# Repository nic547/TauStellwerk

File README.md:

# TauStellwerk

TauStellwerk is a open-source software project for controlling model railways.
It is intended to provide a intuitive user interface for easy and quick edits and control of a model railway.
It is not intended to be a competitor to more complex software like JMRI, TrainController or similar, but rather
an alternative to manufacturer-provided applications.

If you have any questions, feedback or any other comments, feel free to open a issue or pm me(nic547) on discord.

## Overview

The software is still in an experimental state. There might be some fundamental changes that break existing databases or installations.
Currently there are no prebuilt binaries available.

Currently supported Command Stations:

- ESU Command Station (ECoS)
- DCC++ EX (via USB)

## Requirements
TauStellwerk requires the ASP.NET Core Runtime 8.0 to be installed.
See the [Microsoft .NET Download page](https://dotnet.microsoft.com/en-us/download/dotnet/8.0) for downloads and installation instructions.

### MacOS/iOS

Using the cross-platform .NET software framework does mean that the TauStellwerk-Software should run on MacOS/iOS. Unfortunately I do not have access to either OS, so I cannot test on either OS.

### Webserver

Core of the TauStellwerk software is the TauStellwerk.Server component. It handles communication between the CommandStation and the clients. Can, for example, be run on a Raspberry Pi.

For the sake of simplicity, there are no "accounts". Any user can choose whatever username he desires. Access control has be done by restricting access to the server.

### Webapp

The Webapp is based on Blazor WebAssembly and should run on any recent version of the commonly used Browsers. Generally the application is tested with current versions of Chrome, Firefox and Edge. It's expected that the webapp will not necessarily have feature-parity with the dedicated applications and be more of a "lite" version.

### Desktop Application

Uses .NET and AvaloniaUI. Connects to the TauStellwerk.Server. Tested on Linux and Windows.

### Mobile App

Planned but not started. Initially MAUI was intended to be used, currently waiting to see how MAUI vs UNO vs AvaloniaUI for mobile apps pans out.

## Licences

Unless noted otherwise, this project is licensed under the GNU GPLv3, see [here](/LICENSE) for more details.

## Contributing

All contributions are welcome. As I'm currently the sole user and developer, documentation isn't a huge focus for me, so feel free approach me with any potential questions.

## Acknowledgements

JetBrains has been kind enough to provide me with a free open-source license for their products as part of their [open source support program](https://jb.gg/OpenSourceSupport). I'm using Rider for development and can only recommend it.

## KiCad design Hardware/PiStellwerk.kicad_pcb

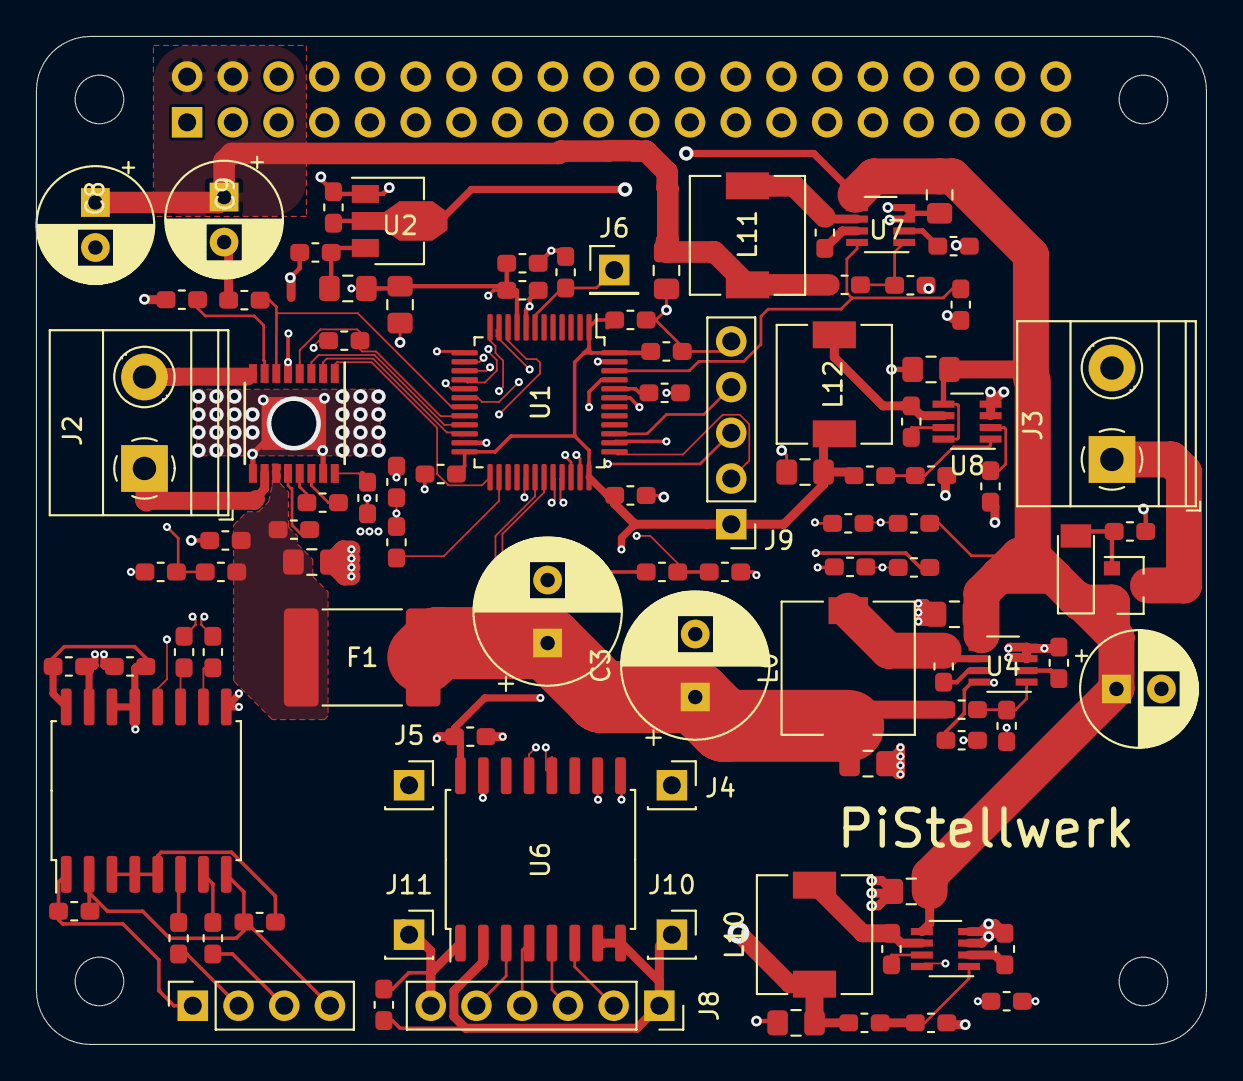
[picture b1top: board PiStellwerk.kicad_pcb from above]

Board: 4 copper layers, 65.0 x 56.0 mm, 104 parts (1 on the bottom side), 78 nets.

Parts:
C1, C4, C5, C6, C18, C19, C20, C27, C28, C29, C30, C31, C32, C33, C35: 35V/100nF; C_0603_1608Metric_Pad1.05x0.95mm_HandSolder
C2, C10, C12, C13, C14, C24: 35V/10uF; C_0805_2012Metric_Pad1.15x1.40mm_HandSolder
C3, C36: 35V/220uF; CP_Radial_D8.0mm_P3.50mm
C7, C17, C21, C26: 6.3V/47uF; C_0805_2012Metric_Pad1.15x1.40mm_HandSolder
C8, C9: 6.3V/470uF; CP_Radial_D6.3mm_P2.50mm
C11, C15, C16, C25, C34: 35V/10nF; C_0603_1608Metric_Pad1.05x0.95mm_HandSolder
C22, C23: C; C_0603_1608Metric_Pad1.05x0.95mm_HandSolder
C41: 35V/100uF; CP_Radial_D6.3mm_P2.50mm
D1: 12V; D_MiniMELF
F1: 24V/3A; Fuse_2920_7451Metric
FB1: Ferrite_Bead; L_0805_2012Metric_Pad1.15x1.40mm_HandSolder
H1, H2, H3, H4: MountingHole; MountingHole_2.7mm_M2.5
J1: Conn_02x20_Odd_Even; PinSocket_2x20_P2.54mm_Vertical
J2, J3: Screw_Terminal_01x02; TerminalBlock_Phoenix_MKDS-1,5-2-5.08_1x02_P5.08mm_Horizont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
J4, J5, J10, J11: Conn_01x01; PinSocket_1x01_P2.54mm_Vertical
J6: Conn_01x01; PinHeader_1x01_P2.54mm_Vertical
J7: Conn_01x04; PinSocket_1x04_P2.54mm_Vertical
J8: Conn_01x06; PinSocket_1x06_P2.54mm_Vertical
J9: Conn_01x05; PinHeader_1x05_P2.54mm_Vertical
L0: 10uH; L_7.3x7.3_H4.5
L10, L11, L12: 3.3uH; L_6.3x6.3_H3
Q1: Q_PMOS_GDS; SOT-23
R1: 2K42; R_0603_1608Metric_Pad1.05x0.95mm_HandSolder
R2, R3, R10, R12, R13, R18, R20, R21, R22, R25, R26: R; R_0603_1608Metric_Pad1.05x0.95mm_HandSolder
R4: 100kOhm; R_0603_1608Metric_Pad1.05x0.95mm_HandSolder
R5, R6, R7, R11: 10K; R_0603_1608Metric_Pad1.05x0.95mm_HandSolder
R8, R14, R16, R19: 100K; R_0603_1608Metric_Pad1.05x0.95mm_HandSolder
R9: 3.4K; R_0603_1608Metric_Pad1.05x0.95mm_HandSolder
R15, R17: 13.7K; R_0603_1608Metric_Pad1.05x0.95mm_HandSolder
R30: 22.1K; R_0603_1608Metric_Pad1.05x0.95mm_HandSolder
R40, R41, R42, R43: 24R; R_0603_1608Metric_Pad1.05x0.95mm_HandSolder
R50, R51, R52, R53: 40K; R_0603_1608Metric_Pad1.05x0.95mm_HandSolder
TH1, TH2: Thermistor_NTC; R_0603_1608Metric_Pad1.05x0.95mm_HandSolder
U1: STM32F103C8Tx; LQFP-48_7x7mm_P0.5mm
U2: HT7533; SOT-89-3
U3: DRV8876; TSSOP-16-1EP_4.4x5mm_P0.65mm
U4, U7, U8, U9: SY8303; TSOT-23-8
U5: ADUM4160; SOIC-16W_7.5x10.3mm_P1.27mm
U6: ISO3088DW; SOIC-16W_7.5x10.3mm_P1.27mm

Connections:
3V3: C4.1, C26.1, C27.2, C28.2, C29.1, C31.1, C32.1, C33.1, J9.1, L12.1, R19.1, U1.1, U1.24, U1.36, U1.48, U5.13, U5.14, U5.16, U6.16
3VA3: C7.1, C34.2, C35.2, FB1.1, TH1.1, TH2.1, U1.9, U3.5
5V: C8.1, C9.1, C17.1, J1.2, J1.4, L11.1, R14.1
18V: C3.1, C13.1, C36.1, F1.1, L0.1, R8.1, R21.1
18V_FUSED: C1.1, C10.1, C22.2, F1.2, R18.1, U3.11
/3V3_UNFILTERED: C6.1, FB1.2, U2.3
/IMODE: R2.1, U3.7
/PMODE: R3.1, U3.16
/TRACK_A: J2.1, U3.10
/TRACK_B: J2.2, U3.8
/USB+: C18.1, J7.1, U5.1
/USB_GND: C18.2, C19.2, J7.4, U5.2, U5.8
/USB_VDD: C19.1, U5.3, U5.4, U5.5
ADC_IN1: R12.2, R13.1, U1.11
ADC_IN2: R21.2, R22.1, U1.12
ADC_IN3: R18.2, R20.1, U1.13
ENABLE_5V: R7.1, U1.46, U7.8
ENABLE_18V: R5.1, U1.38, U4.8
EN_SEC_5V: R11.1, U1.45, U9.8
GND: C1.2, C2.1, C3.2, C4.2, C5.2, C6.2, C7.2, C8.2, C9.2, C10.2, C12.1, C13.2, C14.1, C17.2, C21.2, C24.1, C26.2, C27.1, C28.1, C29.2, C30.2, C31.2, C32.2, C33.2, C34.1, C35.1, C36.2, C41.2, J1.6, J1.9, J1.14, J1.20, J1.25, J1.30, J1.34, J1.39, J3.2, J4.1, J9.5, R1.2, R2.2, R3.2, R4.2, R5.2, R6.2, R7.2, R9.2, R10.1, R11.2, R13.2, R15.2, R17.2, R20.2, R22.2, R30.2, R50.1, R51.1, R52.1, R53.1, U1.8, U1.23, U1.35, U1.47, U2.1, U3.9, U3.15, U3.17, U4.3, U4.4, U5.9, U5.15, U6.9, U6.10, U6.15, U7.3, U7.4, U8.3, U8.4, U9.3, U9.4
IN1: U1.25, U3.1
IN2: U1.22, U3.2
NTC1_ADC: R25.1, TH1.2, U1.10
NTC1_EN: R25.2, U1.26
NTC2_ADC: R26.1, TH2.2, U1.18
NTC2_EN: R26.2, U1.43
unnamed: C11.1, U4.7
unnamed: C11.2, L0.2, U4.6
unnamed: C15.1, U7.7
unnamed: C15.2, L11.2, U7.6
unnamed: C16.1, U9.7
unnamed: C16.2, L10.2, U9.6
unnamed: C20.1, J8.1, J10.1, U6.2, U6.7, U6.8
unnamed: C20.2, J8.6, J11.1, U6.1
unnamed: C21.1, J5.1, L10.1, R16.1
unnamed: C22.1, U3.12
unnamed: C23.1, U3.14
unnamed: C23.2, U3.13
unnamed: C25.1, U8.7
unnamed: C25.2, L12.2, U8.6
unnamed: C30.1, J6.1, U1.7
unnamed: D1.2, Q1.1, R4.1
unnamed: J3.1, Q1.3
unnamed: J7.2, R43.2
unnamed: J7.3, R42.1
unnamed: J8.2, U6.6
unnamed: J8.3, U6.5
unnamed: J8.4, U6.4
unnamed: J8.5, U6.3
unnamed: R6.1, U1.44
unnamed: R8.2, R9.1, U4.1
unnamed: R14.2, R15.1, U7.1
unnamed: R16.2, R17.1, U9.1
unnamed: R19.2, R30.1, U8.1
unnamed: R40.2, U5.11
unnamed: R41.1, U5.10
unnamed: R42.2, U5.7
unnamed: R43.1, U5.6
unnamed: R50.2, U7.2
unnamed: R51.2, U8.2
unnamed: R52.2, U9.2
unnamed: R53.2, U4.2
SPI_MISO: J1.21, U1.16
SPI_MOSI: J1.19, U1.17
SPI_SCLK: J1.23, U1.15
SPI_SS: J1.24, U1.14
SWCLK: J9.2, U1.37
SWDIO: J9.3, U1.34
TRACESWO: J9.4, U1.39
TRACK_CURRENT: R1.1, U1.19, U3.6
UART_RX: U1.31, U6.12
UART_TX: U1.30, U6.13
USB_D+: R41.2, U1.33
USB_D-: R40.1, U1.32
USB_PIN: U1.29, U5.12
VIN: C2.2, C5.1, C12.2, C14.2, C24.2, C41.1, D1.1, Q1.2, R12.1, U2.2, U4.5, U7.5, U8.5, U8.8, U9.5
nFault: R10.2, U1.20, U3.4
nSleep: U1.21, U3.3

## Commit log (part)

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2021-08-18 Bump Avalonia.Desktop from 0.10.6 to 0.10.7
    Bumps [Avalonia.Desktop](https://github.com/AvaloniaUI/Avalonia) from 0.10.6 to 0.10.7.
    - [Release notes](https://github.com/AvaloniaUI/Avalonia/releases)
    - [Commits](https://github.com/AvaloniaUI/Avalonia/compare/0.10.6...0.10.7)
    ---
    updated-dependencies:
    - dependency-name: Avalonia.Desktop
2021-08-20 Update build.sh, only use PublishSingeFile in Relase mode
    Also disable PublishSingleFile for CI
2021-08-24 Delete dependabot.yml
    Resolves #126
2021-08-24 Ensure correct command system status is loaded on startup
    The first StatusChanged event fired before the StatusService was subscribed.
    Instead the StatusSystem can now "ask" for the event.
    Resolves #119
2021-08-29 Replace "Random User $Number" with "Random $color $animal"
    IMHO the new random user names are much easier to remember then a long number. I'm not 100% happy with it, but failed to come up with something better.
    Resolve #132
2021-09-03 Add SonarScanner action .yml (#136)
    * Add SonarScanner action .yml
    * Update sonar.yml
    * Update sonar.yml
2021-09-11 [Desktop] Fix some warnings
2021-09-19 Add explicit trim mode to publish.sh
2021-09-19 Add builds for musl-based linuxes
2021-09-26 Use 5.0.206 instead of 5.0.400 as minimum sdk version
2021-10-02 Replace Blazored.LocalStorage with some basic js and js-interop
2021-10-05 Remove unecessary reference
2021-10-05 Remove the duplicate Tags from EngineEditViewModel
2021-10-07 Interfacify Timer and mock it in the CoalescingLimiterTests
    This should fix the random test failures
2021-10-08 Fix some new warnings + CI
2021-10-13 Update dependencies
    AvaloniaUI-related packages 0.10.7 to 0.10.8
    Microsoft packages rc1 to rc2
2021-10-16 Use file-scoped namespaces
2021-10-25 {Desktop} use IViewService in the MainViewModel
2021-10-26 Remove ReactiveUI
    Resolves #167
2021-10-26 [Desktop] Add tooltips with explanations to settings
    Resolve #142
2021-10-27 Add missing MIME type to AddOrUpdate
2021-11-09 Upgrade to non-prerelease
    Only CommandLineParser and StyleCop versions used are still pre-release
2021-11-22 Update engine-related things to use SignalR
2021-11-23 Rename HttpClientService
    Also fix some other small suggestions
2021-11-29 [WebClient] Improve location and size of E-Stop button
2021-12-11 [WebClient] Add some space below the image in the EngineControl
2021-12-14 [WebClient] Set <select> font-size to 1em
    Resolves #188
2021-12-18 [WebClient] Adjust header of the engine control component
2022-01-01 [WebClient] Fix direction buttons
    In Firefox, the direction buttons didn't fit into the column.
2022-01-03 Fix ECoSConnectionHandler
    Also ensure the test fails more reliable. Before the sending was so fast the "split char" was read as one part.
2022-01-09 Use JsonContext for SignalR (maybe?)
    No Idea if this actually works.
    Resolves #189
2022-01-11 Use fallback image if picture fails to load
    Resolves #196
2022-01-16 [WebClient] Keep state (local) of speed and direction.
2022-01-18 [WebClient] Keep local Function state
2022-01-20 Fix EngineServiceTests by actually adding function to test data
2022-02-08 [WebClient] Allow toggling display of "hidden" engines
    Resolves #25
    Also remove a NuGet-Package that is no longer used
2022-02-15 Fix multiline ECoS messages
    Resolves #211
2022-02-19 Use a sperate EngineImage class on clients instad of the dto.
2022-02-22 Revert commiting local appsettings.json
2022-02-28 Fix Rider warnings for WebClient
2022-03-04 [WebClient] Add placeholder text if no functions are defined
    Resolves #223
2022-03-10 Reset engine when acquried without prior state
    Resolves #220
2022-03-15 Add Semaphore to DccExSerial for writing to serial port.
2022-03-20 Get LoadTester working again, fix other small things
2022-03-22 Fix #230
    Moving the "duplicate change ignoring" one level up should make it work, because Clients can explicitly load the State instead of only relying on "change notifications"
2022-04-12 Update dependencies
    This includes updates for StyleCop and ToolKit.Mvvm to their current preview versions.
2022-04-13 Use Pooling for DbContext
    Resolves #234
2022-04-30 [WebClient] Fix and adjust breakpoints
    WHile adjusting the breakpoints previously, I forgott about the .selection-grid breakpoints, leading to size and count of columns not fitting together.
    Aslo adjust the breakpoints slightly.
2022-05-02 [WebClient] Properly center speed slider
    Also adjust direction buttons to be wider (as wide as possible).
    Update the screenshots with the new images.
    Resolve #244
2022-05-02 Fix clients not actually being able to delete engines
2022-05-04 Implement forget loco command for DccExSerialSystem
    Resolves #235
    Dcc++ EX sends a estop when forgetting to the engine being forgotten (actually twice). So I would expect engines to actually be stopped when forgotten about.
    When a engine is released that still has a non-zero speed the "forget loco" command is not sent - under the assumption that a estop isn't desired and a user will take over control again soonish.
2022-06-25 Rename and move things around
    Reolves #250
    Removed TauStellwerk.Images and TauStellwerk.Database, because their only useful for the server project.
    Rename and restructure the CommandStation parts
2022-07-03 Fix warnings I missed
2022-07-07 Fix ECoS and DccExSerial command stations still trying to load settings from commandSystem
2022-07-31 Fix turnout addresses not being displayed in edit dialog
    Also set minimum and maximum values
2022-08-02 [Desktop] Adjust window titles
    Resolves #258
2022-08-03 Enable implicit usings
2022-08-12 Add a integration test for turnouts
2022-09-18 Keep track of a turnouts state during runtime
    Doesn't persist trough a restart
    Resolves #266
2022-09-19 [Desktop] Fix some errors in the xamls
2022-09-24 Introduce versioning
    resolves #252
2022-09-25 Fix engine list stretching it's cards vertically
    Resolves #280
2022-09-30 [Desktop] Ensure buttons in the list are aligned.
    Resolves #284
2022-10-07 [WebClient] Fix visited links being hard to read due to low contrast
    Resolves #290
2022-10-07 fix: publish script deletes old build artifacts before running builds
2022-10-30 Improve speed of loading the engine list
    Resolves #271
    Tested on a 3900X with a PCIe 3 QLC SSD and 10K engines:
    Using AsSplitQuery seems to work very well.
    Improving the indices lowered the worst case (Ordering by name) from slightly above 40ms to slightly below 20ms.
2022-11-04 upgrade to .NET 7
2022-11-09 Update trimMode for .NET 7
2022-11-16 Use source-generated json serialisation in clients
    - Add some enums to the jsonSerializerContext that don't seem to appear in any other known class
2022-11-20 TestDbTool - add two random tags to every engine
    The two tags simulate using the tags as "alternative names". I personally add the full UIC-number in there - that's where the idea comes from.
    This really should really inflate the table for tags - from my own testing it doubled the time a query takes on a 10K db to around 40ms.
2022-11-23 Add some tests for the TauStellwerk-JsonContext
    The JsonSerializer Context is the source-generator json serializer (for trimming)
2022-12-24 update dto-json-roundtrip tests to use jsonContext
    I think that's what they were supposed to use, no idea why i forgot about the JsonContext part
2022-12-27 [WebClient] Fix function placeholder having unnecessary line breaks
    resolves #309
    Also a minor adjustment to the function list
2023-01-20 denormalize engine images
2023-01-21 remove old debug statement
2023-01-27 [WebClient] Clear search before opening
2023-02-07 [Desktop] Engine list now resets scrolling position when changing page
2023-02-07 [Desktop] fix a weird issue with the engine selection layout
    For some reason, if not all engines are being displayed, horizontal resizing causes the wrapLayout to use much more space than it actually needs. Once all of them "remember" that their not supposed t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
    Using an ItemsControl with a WrapPanel rather than an ItemsRepeater with a WrapLayout somehow fixes this. No idea what's happing, I have been randomly trying out stuff.
2023-02-07 Edit MessageBoxVM to use RelayCommand and Observable Property
    For some reason the button refuses to work with the normal function, this commit fixes that.
2023-02-10 [Desktop] Further translations
2023-03-09 [Desktop] Properly handle not updating an engines image
2023-03-12 Fix naming of properties injected via @inject
2023-03-23 Minor refactorings
2023-03-28 Update dependencies, fix broken things
    AvaloniaUI preview5 => preview6, seems like windows now need to be partial classes
    Netvips
2023-04-20 [WebClient] Use prefers-color-scheme for inital darkmode setting
    Resolves #321
2023-04-25 Split up BasicIntegrationTest into multiple Classes and Files
2023-05-05 Don't "Shutdown" NetVips, fix image generation
    After shutting down NetVips it seems it cannot be used again.
2023-05-11 Remove broken StatusIntegrationTest
2023-06-04 Upgrade AvaloniaUI to v11 rc1.1
2023-07-29 Add swiss german (gsw) translation
2023-08-06 Introduce separate test projects for data and commandStations projects
2023-08-27 Introduce cache busting
2023-10-21 Desktop: Use compact density
2023-10-21 Desktop: Replace Avalonias Fluent theme with Semi.Avalonia
2023-11-14 activate more style rules and fix violations
2023-11-15 Fix SignalR trying to deserialize System.Object
2023-11-27 Adjust editorconfig
    IDE0290 (primary constructors) not quite sure about them for now
    file-scoped namespaces are what the code has been using.
2024-01-01 Ensure top menu is always "touching" window borders and has some separation from content
2024-01-01 Remove leftover debug statement
2024-01-01 Ensure TopMenu viewModels get cleaned up
2024-01-29 Fix bug in windowSettingService, add a extension to Dictonary
    I don't like the out variables and much rather rely on the nullability
2024-01-29 Desktop: color-code stop buttons
    Resolves #144
2024-02-27 Fix new warnings and hints poping up
2024-03-06 Resolve various hints
2024-03-06 Update TauStellwerk.Desktop and related project files
    - Don't generate DocumentationFiles when in Release Configuration
    - Embed debug information rather than having loose .pdb files lying around
    - On linux, don't call the executable TauStellwerk.Desktop to prevent clashing with *.Desktop files
2024-06-04 Disable small stop button during the lockout period
    Resolves #359
2024-06-14 Use Avalonia.Fonts.Inter to provide Inter as a default font
2024-07-25 downloading backups using the desktop application
    Also fix an issue with the string resources
2024-07-28 Deleting Backups
2024-07-29 Use a checkbox for the large stop button setting in the menu
    Resolves #353
2024-08-04 Fix build error when publishing
